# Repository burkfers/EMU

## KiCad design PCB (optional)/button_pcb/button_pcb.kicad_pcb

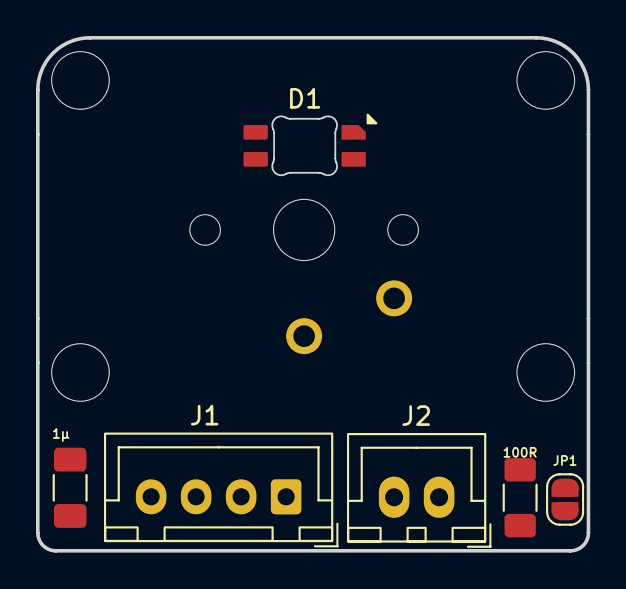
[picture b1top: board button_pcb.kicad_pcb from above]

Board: 2 copper layers, 30.6 x 28.5 mm, 11 parts (1 on the bottom side), 7 nets, no tracks yet.

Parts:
1µ: 1µ; C_1206_3216Metric_Pad1.33x1.80mm_HandSolder
100R: 100; R_1206_3216Metric_Pad1.30x1.75mm_HandSolder
D1: SK6812MINI; LED_choc_6028R
H1, H2, H3, H4: MountingHole; MountingHole_3.2mm_M3_DIN965
J1: RGB connector; JST_XH_B4B-XH-A_1x04_P2.50mm_Vertical
J2: Button connector; JST_XH_B2B-XH-A_1x02_P2.50mm_Vertical
JP1: SolderJumper_2_Open; SolderJumper-2_P1.3mm_Open_RoundedPad1.0x1.5mm
SW1: SW_Push; SW_choc_v1_1u

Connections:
+5V: 1µ.1, D1.4 (VDD), J1.4
/DIN: D1.3 (DIN), J1.2
/DOUT: 100R.2, J1.1
/sw1: J2.2, SW1.2
/sw_gnd: J2.1, JP1.2 (B), SW1.1
GND: 1µ.2, D1.2 (VSS), J1.3, JP1.1 (A)
unnamed: 100R.1, D1.1 (DOUT)

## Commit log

2026-02-20 add button pcb wip
